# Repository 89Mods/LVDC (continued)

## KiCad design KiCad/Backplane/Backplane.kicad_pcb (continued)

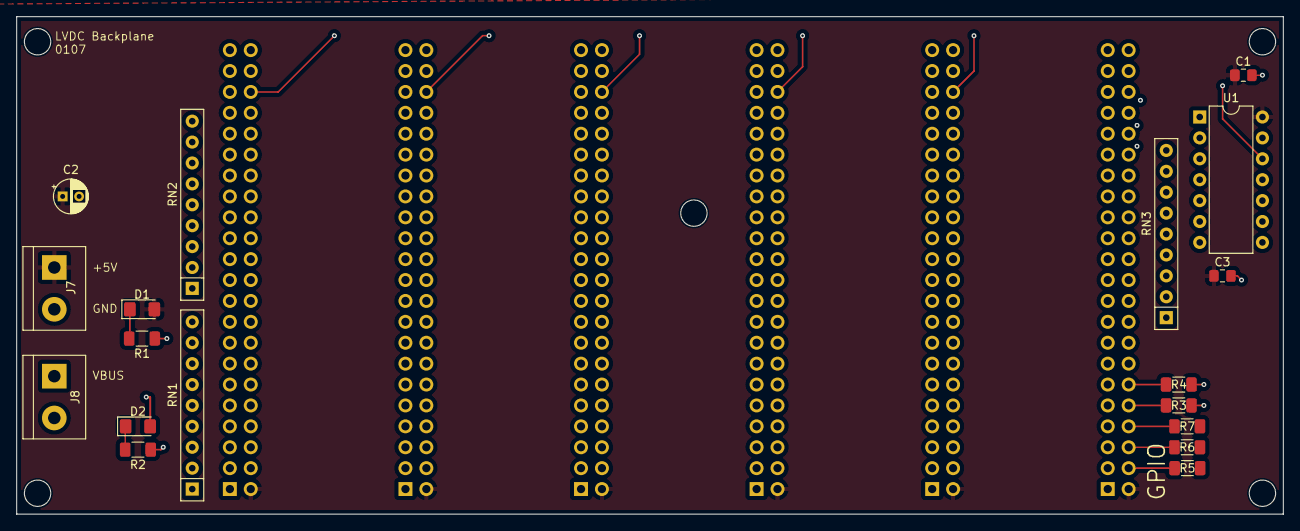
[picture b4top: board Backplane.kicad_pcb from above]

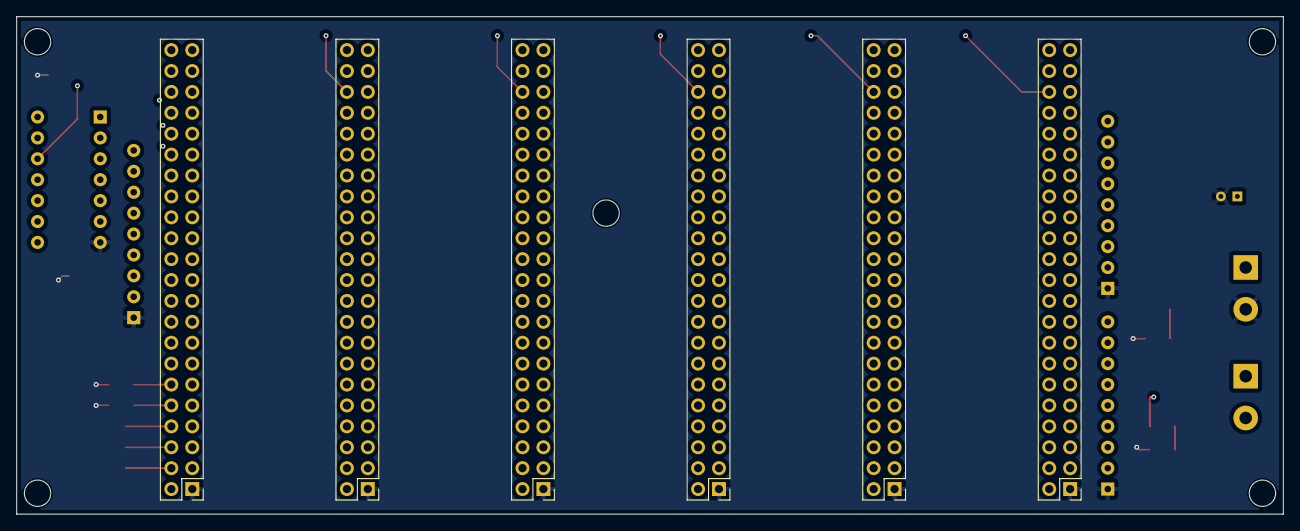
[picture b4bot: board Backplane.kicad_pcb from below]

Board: 4 copper layers, 153.9 x 60.5 mm, 24 parts (6 on the bottom side), 52 nets.

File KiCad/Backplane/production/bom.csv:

Designator,Footprint,Quantity,Value,LCSC Part #
"_5, _4, _3, _2, ",,5,,
C1,0805,1,100nF,
C2,CP_Radial_D4.0mm_P2.00mm,1,10µF,
C3,0805,1,1µF,
"D1, D2",1206,2,LED,
J1,PinHeader_2x22_P2.54mm_Vertical,1,SLOT1,
J2,PinHeader_2x22_P2.54mm_Vertical,1,SLOT2,
J3,PinHeader_2x22_P2.54mm_Vertical,1,SLOT3,
J4,PinHeader_2x22_P2.54mm_Vertical,1,SLOT4,
J5,PinHeader_2x22_P2.54mm_Vertical,1,SLOT5,
J6,PinHeader_2x22_P2.54mm_Vertical,1,GPIO,
"J7, J8",TerminalBlock_bornier-2_P5.08mm,2,Screw_Terminal_01x02,
"R1, R2, R3, R4, R5, R6, R7",1206,7,2K,
"RN1, RN2, RN3",R_Array_SIP9,3,R_Network08,
U1,DIP-14_W7.62mm,1,74HCT04,

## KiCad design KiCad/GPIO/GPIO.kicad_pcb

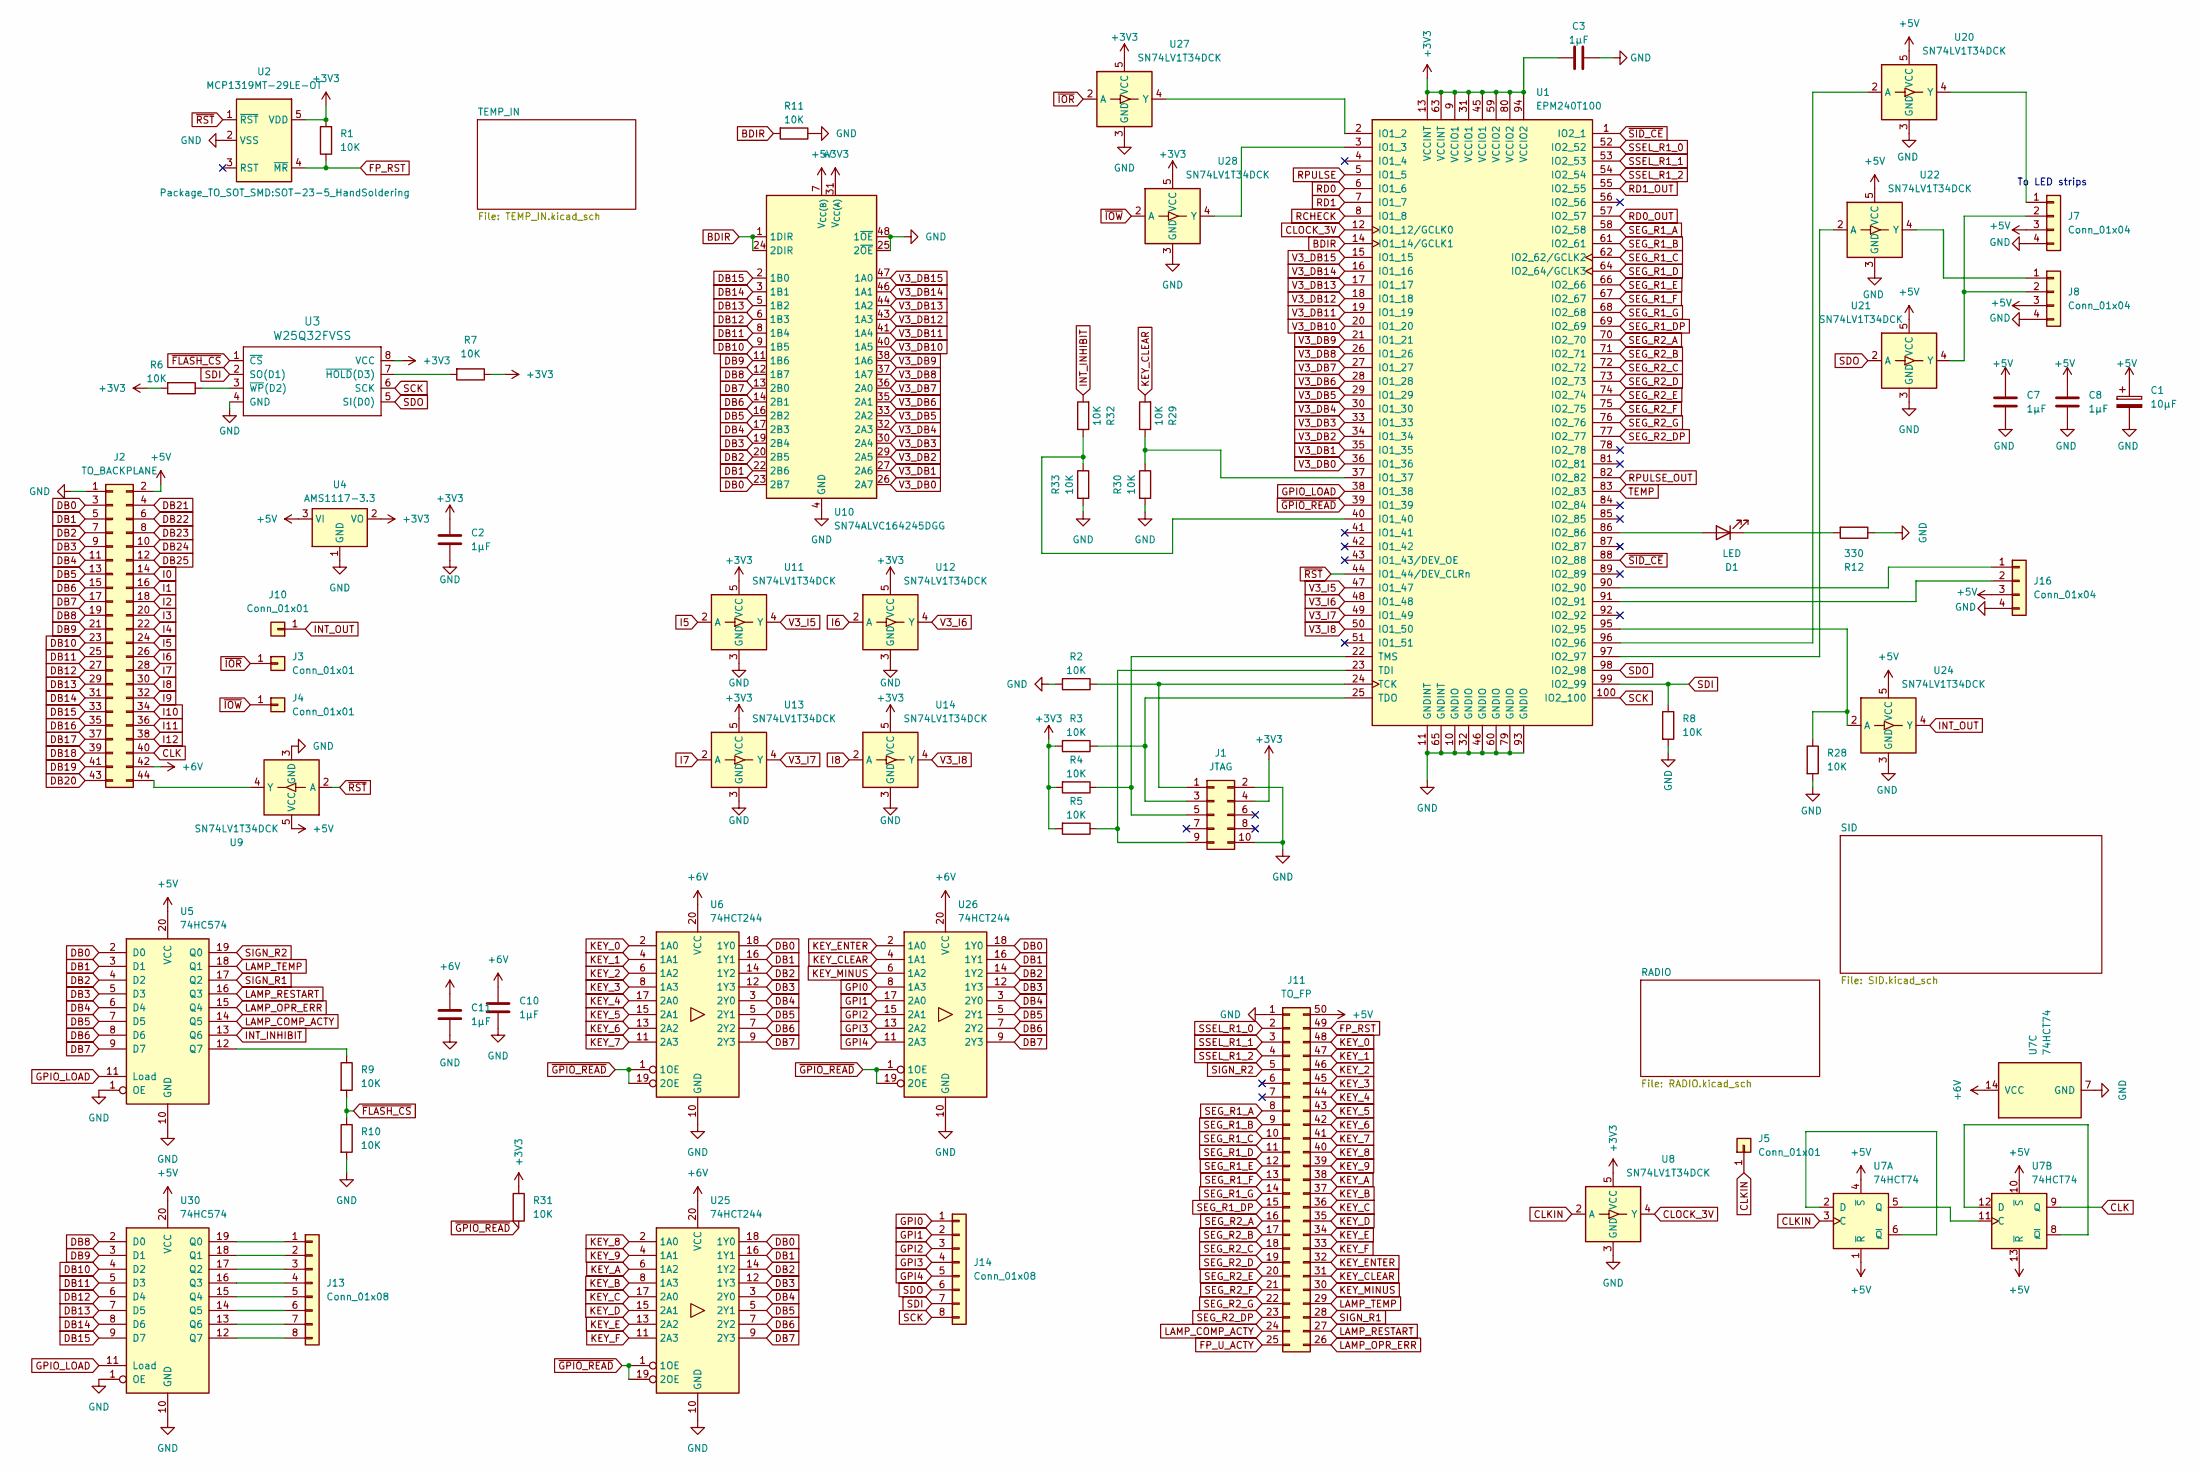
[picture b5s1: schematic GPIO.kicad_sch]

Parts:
C1: 10µF; CP_Radial_D4.0mm_P2.00mm
C2, C3, C7, C8, C10, C11: 1µF; C_0805_2012Metric_Pad1.18x1.45mm_HandSolder
D1: LED; LED_1206_3216Metric_Pad1.42x1.75mm_HandSolder
J1: JTAG; PinHeader_2x05_P2.54mm_Vertical
J2: TO_BACKPLANE; PinHeader_2x22_P2.54mm_Vertical
J3, J4, J5, J10: Conn_01x01; PinHeader_1x01_P2.54mm_Vertical
J7, J8, J16: Conn_01x04; PinHeader_1x04_P2.54mm_Vertical
J11: TO_FP; PinHeader_2x25_P2.54mm_Vertical
J13, J14: Conn_01x08; PinHeader_1x08_P2.54mm_Vertical
R1, R2, R3, R4, R5, R6, R7, R8, R9, R10, R11, R28, R29, R30, R31, R32, R33: 10K; R_1206_3216Metric_Pad1.30x1.75mm_HandSolder
R12: 330; R_1206_3216Metric_Pad1.30x1.75mm_HandSolder
U1: EPM240T100; LQFP-100_14x14mm_P0.5mm
U2: MCP1319MT-29LE-OT; SOT-23-5_HandSoldering
U3: W25Q32FVSS; DIP-8_W7.62mm_Socket; Part # W25Q32JVSSIQ
U4: AMS1117-3.3; SOT-223-3_TabPin2
U5, U30: 74HC574; SO-20_12.8x7.5mm_P1.27mm
U6, U25, U26: 74HCT244; SO-20_12.8x7.5mm_P1.27mm
U7: 74HCT74; SO-14_3.9x8.65mm_P1.27mm
U8, U9, U11, U12, U13, U14, U20, U21, U22, U24, U27, U28: SN74LV1T34DCK; SOT-23-5
U10: SN74ALVC164245DGG; TSSOP-48_6.1x12.5mm_P0.5mm

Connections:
+3V3: C2.2, C3.2, J1.4, R1.2, R3.2, R4.2, R5.2, R6.2, R7.1, R31.1, U1.9 (VCCIO1), U1.13 (VCCINT), U1.31 (VCCIO1), U1.45 (VCCIO1), U1.59 (VCCIO2), U1.63 (VCCINT), U1.80 (VCCIO2), U1.94 (VCCIO2), U2.5 (VDD), U3.8 (VCC), U4.2 (VO), U8.5 (VCC), U10.31 (V_{CC(A)}), U10.42 (V_{CC(A)}), U11.5 (VCC), U12.5 (VCC), U13.5 (VCC), U14.5 (VCC), U27.5 (VCC), U28.5 (VCC); also elsewhere on the board
+5V: C1.1, C7.2, C8.2, J2.2, J7.3, J8.3, J11.50, J16.3, U4.3 (VI), U5.20 (VCC), U7.1 (~R), U7.4 (~S), U7.10 (~S), U7.13 (~R), U9.5 (VCC), U10.7 (V_{CC(B)}), U10.18 (V_{CC(B)}), U20.5 (VCC), U21.5 (VCC), U22.5 (VCC), U24.5 (VCC), U30.20 (VCC); also elsewhere on the board
+6V: C10.2, C11.2, J2.42, U6.20 (VCC), U7.14 (VCC), U25.20 (VCC), U26.20 (VCC)
BDIR: R11.2, U1.14 (IO1_14/GCLK1), U10.1 (1DIR), U10.24 (2DIR)
CLK: J2.40, U7.9 (Q)
CLKIN: J5.1, U7.3 (C), U8.2 (A)
CLOCK_3V: U1.12 (IO1_12/GCLK0), U8.4 (Y)
DB0: J2.3, U5.2 (D0), U6.18 (1Y0), U10.23 (2B7), U25.18 (1Y0), U26.18 (1Y0); also elsewhere on the board
DB1: J2.5, U5.3 (D1), U6.16 (1Y1), U10.22 (2B6), U25.16 (1Y1), U26.16 (1Y1); also elsewhere on the board
DB2: J2.7, U5.4 (D2), U6.14 (1Y2), U10.20 (2B5), U25.14 (1Y2), U26.14 (1Y2); also elsewhere on the board
DB3: J2.9, U5.5 (D3), U6.12 (1Y3), U10.19 (2B4), U25.12 (1Y3), U26.12 (1Y3); also elsewhere on the board
DB4: J2.11, U5.6 (D4), U6.3 (2Y0), U10.17 (2B3), U25.3 (2Y0), U26.3 (2Y0); also elsewhere on the board
DB5: J2.13, U5.7 (D5), U6.5 (2Y1), U10.16 (2B2), U25.5 (2Y1), U26.5 (2Y1); also elsewhere on the board
DB6: J2.15, U5.8 (D6), U6.7 (2Y2), U10.14 (2B1), U25.7 (2Y2), U26.7 (2Y2); also elsewhere on the board
DB7: J2.17, U5.9 (D7), U6.9 (2Y3), U10.13 (2B0), U25.9 (2Y3), U26.9 (2Y3); also elsewhere on the board
DB8: J2.19, U10.12 (1B7), U30.2 (D0); also elsewhere on the board
DB9: J2.21, U10.11 (1B6), U30.3 (D1); also elsewhere on the board
DB10: J2.23, U10.9 (1B5), U30.4 (D2); also elsewhere on the board
DB11: J2.25, U10.8 (1B4), U30.5 (D3); also elsewhere on the board
DB12: J2.27, U10.6 (1B3), U30.6 (D4); also elsewhere on the board
DB13: J2.29, U10.5 (1B2), U30.7 (D5); also elsewhere on the board
DB14: J2.31, U10.3 (1B1), U30.8 (D6)
DB15: J2.33, U10.2 (1B0), U30.9 (D7)
DB16: J2.35
DB17: J2.37
DB18: J2.39
DB19: J2.41
DB20: J2.43
DB21: J2.4
DB22: J2.6
DB23: J2.8
DB24: J2.10
DB25: J2.12
FP_RST: J11.49, R1.1, U2.4 (~MR)
FP_U_ACTY: J11.25; also elsewhere on the board
GND: C1.2, C2.1, C3.1, C7.1, C8.1, C10.1, C11.1, J1.2, J1.10, J2.1, J7.4, J8.4, J11.1, J16.4, R2.2, R8.2, R10.2, R11.1, R12.1, R28.2, R30.2, R33.2, U1.10 (GNDIO), U1.11 (GNDINT), U1.32 (GNDIO), U1.46 (GNDIO), U1.60 (GNDIO), U1.65 (GNDINT), U1.79 (GNDIO), U1.93 (GNDIO), U2.2 (VSS), U3.4 (GND), U4.1 (GND), U5.1 (OE), U5.10 (GND), U6.10 (GND), U7.7 (GND), U8.3 (GND), U9.3 (GND), U10.4 (GND), U10.10 (GND), U10.15 (GND), U10.21 (GND), U10.25 (2~OE), U10.28 (GND), U10.34 (GND), U10.39 (GND), U10.45 (GND), U10.48 (1~OE), U11.3 (GND), U12.3 (GND), U13.3 (GND), U14.3 (GND), U20.3 (GND), U21.3 (GND), U22.3 (GND), U24.3 (GND), U25.10 (GND), U26.10 (GND), U27.3 (GND), U28.3 (GND), U30.1 (OE), U30.10 (GND); also elsewhere on the board
GPI0: J14.1, U26.8 (1A3)
GPI1: J14.2, U26.17 (2A0)
GPI2: J14.3, U26.15 (2A1)
GPI3: J14.4, U26.13 (2A2)
GPI4: J14.5, U26.11 (2A3)
GPIO_LOAD: U1.38 (IO1_38), U5.11 (Load), U30.11 (Load)
I0: J2.14
I1: J2.16
I2: J2.18
I3: J2.20
I4: J2.22
I5: J2.24, U11.2 (A)
I6: J2.26, U12.2 (A)
I7: J2.28, U13.2 (A)
I8: J2.30, U14.2 (A)
I9: J2.32
I10: J2.34
I11: J2.36
I12: J2.38
INT_INHIBIT: R32.2, U5.13 (Q6)
INT_OUT: J10.1, U24.4 (Y)
KEY_0: J11.48, U6.2 (1A0)
KEY_1: J11.47, U6.4 (1A1)
KEY_2: J11.46, U6.6 (1A2)
KEY_3: J11.45, U6.8 (1A3)
KEY_4: J11.44, U6.17 (2A0)
KEY_5: J11.43, U6.15 (2A1)
KEY_6: J11.42, U6.13 (2A2)
KEY_7: J11.41, U6.11 (2A3)
KEY_8: J11.40, U25.2 (1A0)
KEY_9: J11.39, U25.4 (1A1)
KEY_A: J11.38, U25.6 (1A2)
KEY_B: J11.37, U25.8 (1A3)
KEY_C: J11.36, U25.17 (2A0)
KEY_CLEAR: J11.31, R29.2, U26.4 (1A1)
KEY_D: J11.35, U25.15 (2A1)
KEY_E: J11.34, U25.13 (2A2)
KEY_ENTER: J11.32, U26.2 (1A0)
KEY_F: J11.33, U25.11 (2A3)
KEY_MINUS: J11.30, U26.6 (1A2)
LAMP_COMP_ACTY: J11.24, U5.14 (Q5)
LAMP_OPR_ERR: J11.26, U5.15 (Q4)
LAMP_RESTART: J11.27, U5.16 (Q3)
LAMP_TEMP: J11.29, U5.18 (Q1)
unnamed: D1.2 (A), U1.86 (IO2_86)
unnamed: D1.1 (K), R12.2
unnamed: J1.1, R2.1, U1.24 (TCK)
unnamed: J1.3, R3.1, U1.25 (TDO)
unnamed: J1.5, R4.1, U1.22 (TMS)
unnamed: J1.9, R5.1, U1.23 (TDI)
unnamed: J2.44, U9.4 (Y)
unnamed: J7.1, U20.4 (Y)
unnamed: J7.2, J8.2, U21.4 (Y)
unnamed: J8.1, U22.4 (Y)
unnamed: J13.1, U30.19 (Q0)
unnamed: J13.2, U30.18 (Q1)
unnamed: J13.3, U30.17 (Q2)
unnamed: J13.4, U30.16 (Q3)
unnamed: J13.5, U30.15 (Q4)
unnamed: J13.6, U30.14 (Q5)
unnamed: J13.7, U30.13 (Q6)
unnamed: J13.8, U30.12 (Q7)
unnamed: J16.1, U1.90 (IO2_90)
unnamed: J16.2, U1.91 (IO2_91)
unnamed: U1.2 (IO1_2), U27.4 (Y)
unnamed: U1.3 (IO1_3), U28.4 (Y)
unnamed: R29.1, R30.1, U1.37 (IO1_37)
unnamed: R32.1, R33.1, U1.40 (IO1_40)
unnamed: R28.1, U1.95 (IO2_95), U24.2 (A)
unnamed: U1.96 (IO2_96), U20.2 (A)
unnamed: U1.97 (IO2_97), U22.2 (A)
unnamed: R7.2, U3.7 (~HOLD(D3))
unnamed: R6.1, U3.3 (~WP(D2))
unnamed: R9.1, U5.12 (Q7)
unnamed: U7.2 (D), U7.6 (~Q)
unnamed: U7.5 (Q), U7.11 (C)
unnamed: U7.8 (~Q), U7.12 (D)
RCHECK: U1.8 (IO1_8); also elsewhere on the board
RD0: U1.6 (IO1_6); also elsewhere on the board
RD0_OUT: U1.57 (IO2_57); also elsewhere on the board
RD1: U1.7 (IO1_7); also elsewhere on the board
RD1_OUT: U1.55 (IO2_55); also elsewhere on the board
RPULSE: U1.5 (IO1_5); also elsewhere on the board
RPULSE_OUT: U1.82 (IO2_82); also elsewhere on the board
SCK: J14.8, U1.100 (IO2_100), U3.6 (SCK)
SDI: J14.7, R8.1, U1.99 (IO2_99), U3.2 (SO(D1))
SDO: J14.6, U1.98 (IO2_98), U3.5 (SI(D0)), U21.2 (A)
SEG_R1_A: J11.8, U1.58 (IO2_58)
SEG_R1_B: J11.9, U1.61 (IO2_61)
SEG_R1_C: J11.10, U1.62 (IO2_62/GCLK2)
SEG_R1_D: J11.11, U1.64 (IO2_64/GCLK3)
SEG_R1_DP: J11.15, U1.69 (IO2_69)
SEG_R1_E: J11.12, U1.66 (IO2_66)
SEG_R1_F: J11.13, U1.67 (IO2_67)
SEG_R1_G: J11.14, U1.68 (IO2_68)
SEG_R2_A: J11.16, U1.70 (IO2_70)
SEG_R2_B: J11.17, U1.71 (IO2_71)
SEG_R2_C: J11.18, U1.72 (IO2_72)
SEG_R2_D: J11.19, U1.73 (IO2_73)
SEG_R2_DP: J11.23, U1.77 (IO2_77)
SEG_R2_E: J11.20, U1.74 (IO2_74)
SEG_R2_F: J11.21, U1.75 (IO2_75)
SEG_R2_G: J11.22, U1.76 (IO2_76)
SIGN_R1: J11.28, U5.17 (Q2)
SIGN_R2: J11.5, U5.19 (Q0)
SSEL_R1_0: J11.2, U1.52 (IO2_52)
SSEL_R1_1: J11.3, U1.53 (IO2_53)
SSEL_R1_2: J11.4, U1.54 (IO2_54)
TEMP: U1.83 (IO2_83); also elsewhere on the board
V3_DB0: U1.36 (IO1_36), U10.26 (2A7)
V3_DB1: U1.35 (IO1_35), U10.27 (2A6)
V3_DB2: U1.34 (IO1_34), U10.29 (2A5)
V3_DB3: U1.33 (IO1_33), U10.30 (2A4)
V3_DB4: U1.30 (IO1_30), U10.32 (2A3)
V3_DB5: U1.29 (IO1_29), U10.33 (2A2)
V3_DB6: U1.28 (IO1_28), U10.35 (2A1)
V3_DB7: U1.27 (IO1_27), U10.36 (2A0)
V3_DB8: U1.26 (IO1_26), U10.37 (1A7)
V3_DB9: U1.21 (IO1_21), U10.38 (1A6)
V3_DB10: U1.20 (IO1_20), U10.40 (1A5)
V3_DB11: U1.19 (IO1_19), U10.41 (1A4)
V3_DB12: U1.18 (IO1_18), U10.43 (1A3)
V3_DB13: U1.17 (IO1_17), U10.44 (1A2)
V3_DB14: U1.16 (IO1_16), U10.46 (1A1)
V3_DB15: U1.15 (IO1_15), U10.47 (1A0)
V3_I5: U1.47 (IO1_47), U11.4 (Y)
V3_I6: U1.48 (IO1_48), U12.4 (Y)
V3_I7: U1.49 (IO1_49), U13.4 (Y)
V3_I8: U1.50 (IO1_50), U14.4 (Y)
~FLASH_CS: R9.2, R10.1, U3.1 (~CS)
~GPIO_READ: R31.2, U1.39 (IO1_39), U6.1 (1OE), U6.19 (2OE), U25.1 (1OE), U25.19 (2OE), U26.1 (1OE), U26.19 (2OE)
~IOR: J3.1, U27.2 (A)
~IOW: J4.1, U28.2 (A); also elsewhere on the board
~RST: U1.44 (IO1_44/DEV_CLRn), U2.1 (~RST), U9.2 (A)
~SID_CE: U1.1 (IO2_1), U1.88 (IO2_88); also elsewhere on the board

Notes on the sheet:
To LED strips

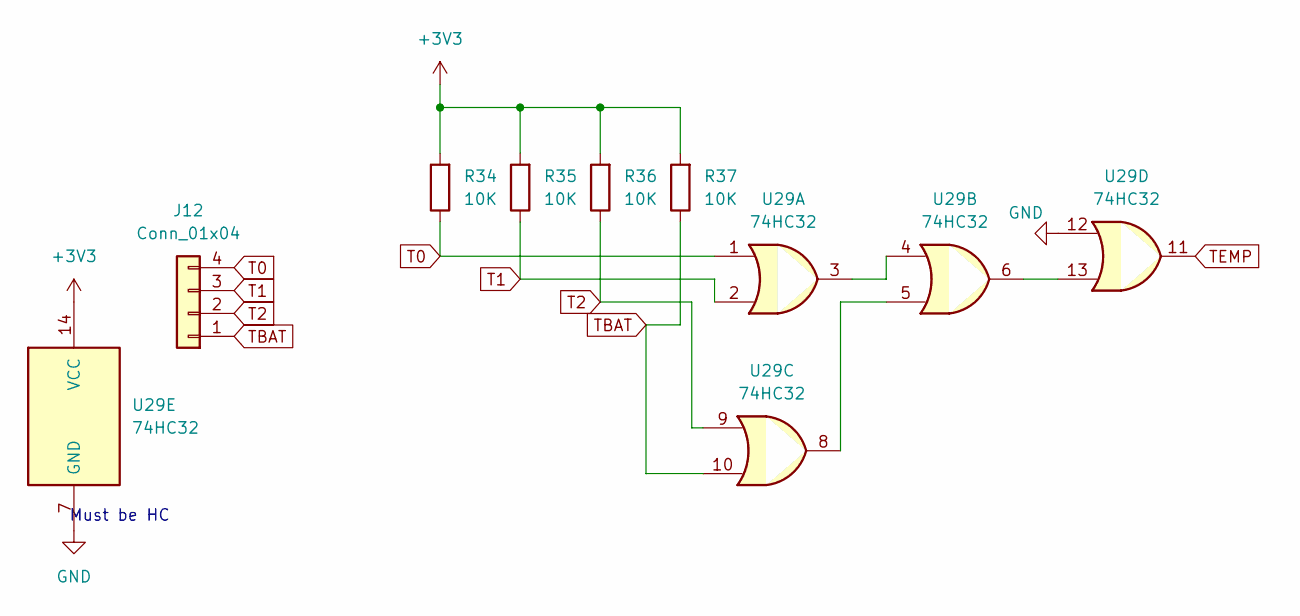
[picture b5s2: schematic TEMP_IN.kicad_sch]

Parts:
J12: Conn_01x04; PinHeader_1x04_P2.54mm_Vertical
R34, R35, R36, R37: 10K; R_1206_3216Metric_Pad1.30x1.75mm_HandSolder
U29: 74HC32; SO-14_3.9x8.65mm_P1.27mm

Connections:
+3V3: R34.2, R35.2, R36.2, R37.2, U29.14 (VCC); also elsewhere on the board
GND: U29.7 (GND), U29.12; also elsewhere on the board
unnamed: U29.3, U29.4
unnamed: U29.5, U29.8
unnamed: U29.6, U29.13
T0: J12.4, R34.1, U29.1
T1: J12.3, R35.1, U29.2
T2: J12.2, R36.1, U29.9
TBAT: J12.1, R37.1, U29.10
TEMP: U29.11; also elsewhere on the board

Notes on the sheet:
Must be HC

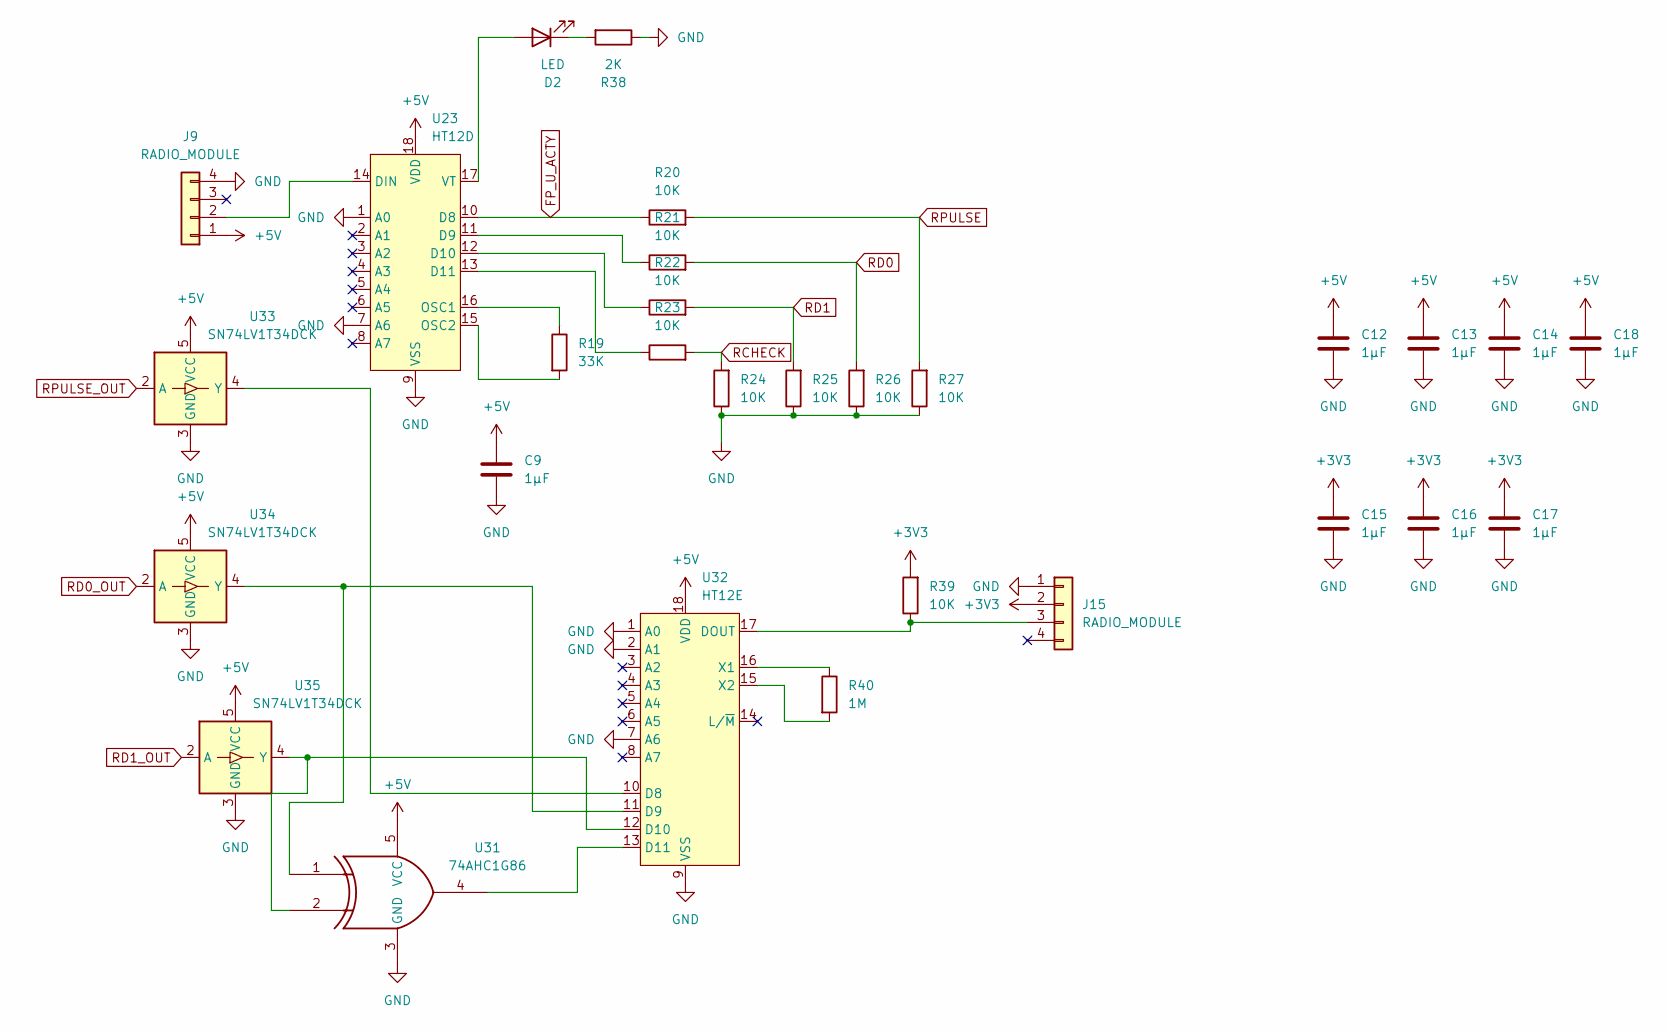
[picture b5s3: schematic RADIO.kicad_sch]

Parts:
C9, C12, C13, C14, C15, C16, C17, C18: 1µF; C_0805_2012Metric_Pad1.18x1.45mm_HandSolder
D2: LED; LED_1206_3216Metric_Pad1.42x1.75mm_HandSolder
J9, J15: RADIO_MODULE; PinSocket_1x04_P2.54mm_Vertical
R19: 33K; R_1206_3216Metric_Pad1.30x1.75mm_HandSolder
R20, R21, R22, R23, R24, R25, R26, R27, R39: 10K; R_1206_3216Metric_Pad1.30x1.75mm_HandSolder
R38: 2K; R_1206_3216Metric_Pad1.30x1.75mm_HandSolder
R40: 1M; R_1206_3216Metric_Pad1.30x1.75mm_HandSolder
U23: HT12D; DIP-18_W7.62mm
U31: 74AHC1G86; SOT-23-5_HandSoldering
U32: HT12E; DIP-18_W7.62mm
U33, U34, U35: SN74LV1T34DCK; SOT-23-5

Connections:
+3V3: C15.2, C16.2, C17.2, J15.2, R39.2; also elsewhere on the board
+5V: C9.2, C12.2, C13.2, C14.2, C18.2, J9.1, U23.18 (VDD), U31.5 (VCC), U32.18 (VDD), U33.5 (VCC), U34.5 (VCC), U35.5 (VCC); also elsewhere on the board
FP_U_ACTY: R20.1, U23.10 (D8); also elsewhere on the board
GND: C9.1, C12.1, C13.1, C14.1, C15.1, C16.1, C17.1, C18.1, J9.4, J15.1, R24.1, R25.1, R26.1, R27.1, R38.1, U23.1 (A0), U23.7 (A6), U23.9 (VSS), U31.3 (GND), U32.1 (A0), U32.2 (A1), U32.7 (A6), U32.9 (VSS), U33.3 (GND), U34.3 (GND), U35.3 (GND); also elsewhere on the board
unnamed: D2.2 (A), U23.17 (VT)
unnamed: D2.1 (K), R38.2
unnamed: J9.2, U23.14 (DIN)
unnamed: J15.3, R39.1, U32.17 (DOUT)
unnamed: R21.1, U23.11 (D9)
unnamed: R22.1, U23.12 (D10)
unnamed: R23.1, U23.13 (D11)
unnamed: R19.1, U23.16 (OSC1)
unnamed: R19.2, U23.15 (OSC2)
unnamed: U32.10 (D8), U33.4 (Y)
unnamed: U31.1, U32.11 (D9), U34.4 (Y)
unnamed: U31.2, U32.12 (D10), U35.4 (Y)
unnamed: U31.4, U32.13 (D11)
unnamed: R40.1, U32.16 (X1)
unnamed: R40.2, U32.15 (X2)
RCHECK: R23.2, R24.2; also elsewhere on the board
RD0: R21.2, R26.2; also elsewhere on the board
RD0_OUT: U34.2 (A); also elsewhere on the board
RD1: R22.2, R25.2; also elsewhere on the board
RD1_OUT: U35.2 (A); also elsewhere on the board
RPULSE: R20.2, R27.2; also elsewhere on the board
RPULSE_OUT: U33.2 (A); also elsewhere on the board

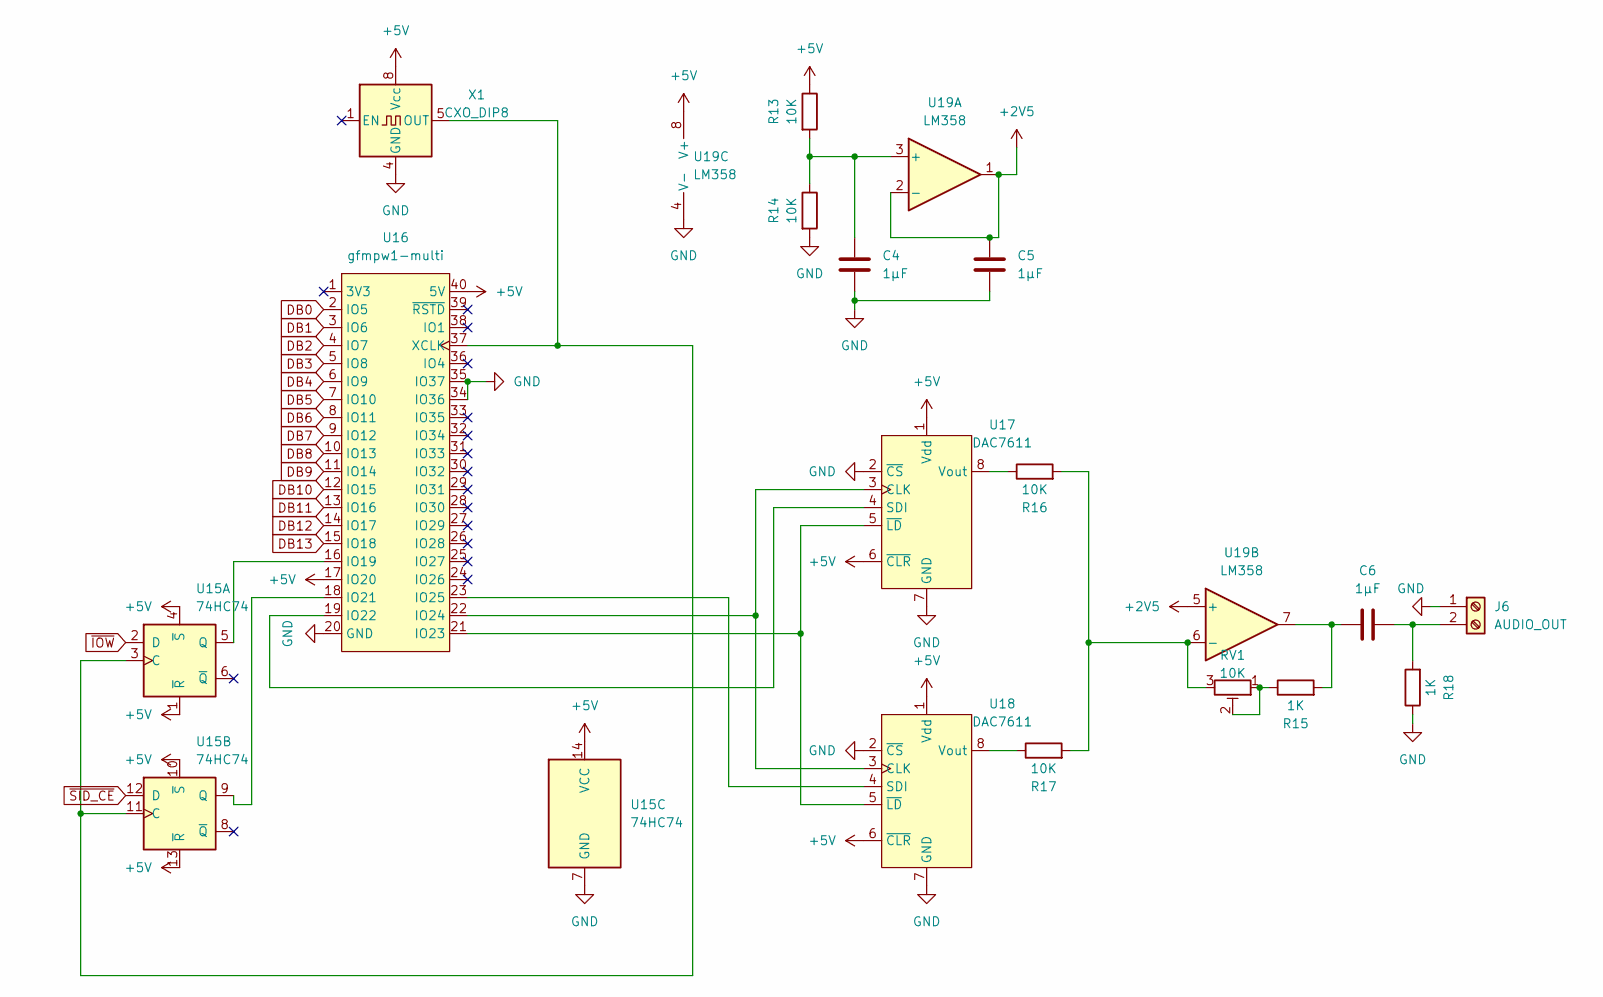
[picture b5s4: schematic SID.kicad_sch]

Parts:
C4, C5, C6: 1µF; C_0805_2012Metric_Pad1.18x1.45mm_HandSolder
J6: AUDIO_OUT; TerminalBlock_bornier-2_P5.08mm
R13, R14, R16, R17: 10K; R_1206_3216Metric_Pad1.30x1.75mm_HandSolder
R15, R18: 1K; R_1206_3216Metric_Pad1.30x1.75mm_HandSolder
RV1: 10K; Potentiometer_ACP_CA9-V10_Vertical
U15: 74HC74; SO-14_3.9x8.65mm_P1.27mm
U16: gfmpw1-multi; DIP-40_W15.24mm_Socket
U17, U18: DAC7611; DIP-8_W7.62mm
U19: LM358; DIP-8_W7.62mm
X1: CXO_DIP8; Oscillator_DIP-8

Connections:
+2V5: C5.2, U19.1, U19.2 (-), U19.5 (+)
+5V: R13.1, U15.1 (~R), U15.4 (~S), U15.10 (~S), U15.13 (~R), U15.14 (VCC), U16.17 (IO20), U16.40 (5V), U17.1 (Vdd), U17.6 (~CLR), U18.1 (Vdd), U18.6 (~CLR), U19.8 (V+), X1.8 (Vcc); also elsewhere on the board
DB0: U16.2 (IO5); also elsewhere on the board
DB1: U16.3 (IO6); also elsewhere on the board
DB2: U16.4 (IO7); also elsewhere on the board
DB3: U16.5 (IO8); also elsewhere on the board
DB4: U16.6 (IO9); also elsewhere on the board
DB5: U16.7 (IO10); also elsewhere on the board
DB6: U16.8 (IO11); also elsewhere on the board
DB7: U16.9 (IO12); also elsewhere on the board
DB8: U16.10 (IO13); also elsewhere on the board
DB9: U16.11 (IO14); also elsewhere on the board
DB10: U16.12 (IO15); also elsewhere on the board
DB11: U16.13 (IO16); also elsewhere on the board
DB12: U16.14 (IO17); also elsewhere on the board
DB13: U16.15 (IO18); also elsewhere on the board
GND: C4.1, C5.1, J6.1, R14.2, R18.1, U15.7 (GND), U16.20 (GND), U16.34 (IO36), U16.35 (IO37), U17.2 (~CS), U17.7 (GND), U18.2 (~CS), U18.7 (GND), U19.4 (V-), X1.4 (GND); also elsewhere on the board
unnamed: C6.2, R15.2, U19.7
unnamed: C6.1, J6.2, R18.2
unnamed: R15.1, RV1.1, RV1.2
unnamed: U15.3 (C), U15.11 (C), U16.37 (XCLK), X1.5 (OUT)
unnamed: U15.5 (Q), U16.16 (IO19)
unnamed: U15.9 (Q), U16.18 (IO21)
unnamed: U16.19 (IO22), U17.4 (SDI)
unnamed: U16.21 (IO23), U17.5 (~LD), U18.5 (~LD)
unnamed: U16.22 (IO24), U17.3 (CLK), U18.3 (CLK)
unnamed: U16.23 (IO25), U18.4 (SDI)
unnamed: R16.1, U17.8 (Vout)
unnamed: R17.1, U18.8 (Vout)
unnamed: C4.2, R13.2, R14.1, U19.3 (+)
unnamed: R16.2, R17.2, RV1.3, U19.6 (-)
~IOW: U15.2 (D); also elsewhere on the board
~SID_CE: U15.12 (D); also elsewhere on the board

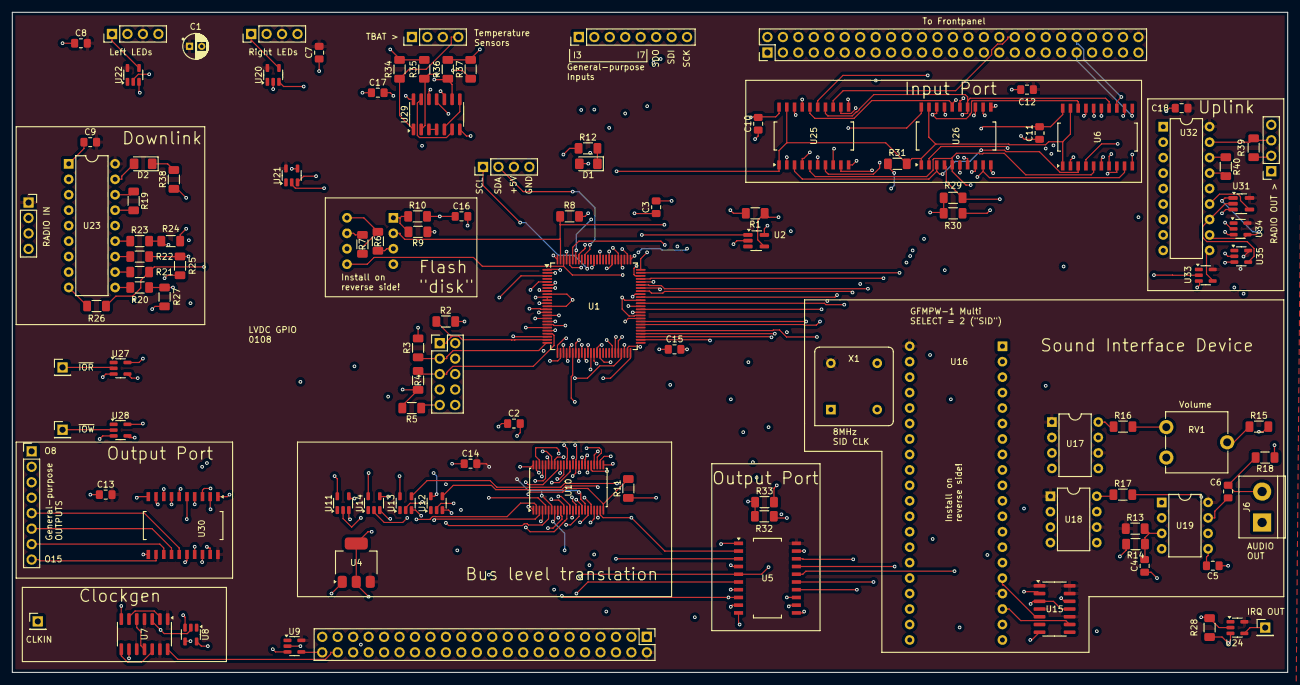
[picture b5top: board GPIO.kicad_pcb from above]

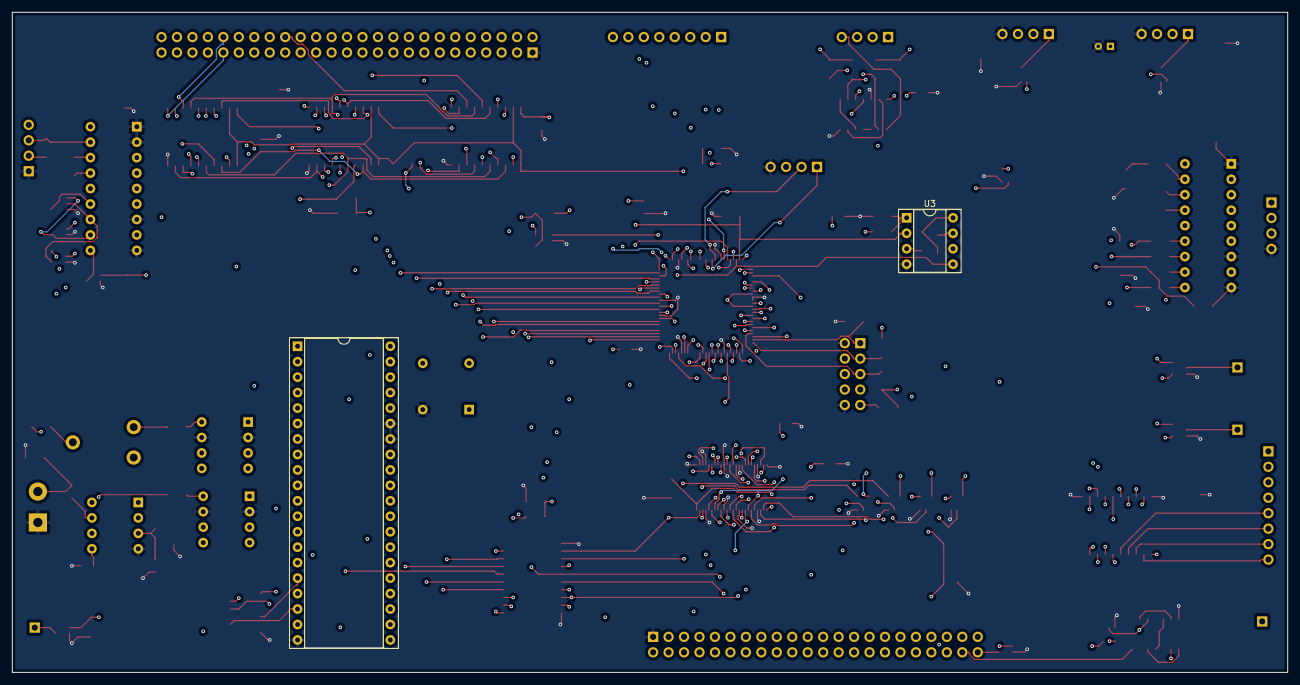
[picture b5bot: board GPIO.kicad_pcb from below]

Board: 4 copper layers, 209.6 x 108.5 mm, 113 parts (2 on the bottom side), 189 nets.

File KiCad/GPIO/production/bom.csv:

Designator,Footprint,Quantity,Value,LCSC Part #
C1,CP_Radial_D4.0mm_P2.00mm,1,10µF,
"C10, C11, C12, C13, C14, C15, C16, C17, C18, C2, C3, C4, C5, C6, C7, C8, C9",0805,17,1µF,
"D1, D2",1206,2,LED,
J1,PinHeader_2x05_P2.54mm_Vertical,1,JTAG,
"J10, J3, J4, J5",PinHeader_1x01_P2.54mm_Vertical,4,Conn_01x01,
J11,PinHeader_2x25_P2.54mm_Vertical,1,TO_FP,
"J12, J16, J7, J8",PinHeader_1x04_P2.54mm_Vertical,4,Conn_01x04,
"J13, J14",PinHeader_1x08_P2.54mm_Vertical,2,Conn_01x08,
"J15, J9",PinSocket_1x04_P2.54mm_Vertical,2,RADIO_MODULE,
J2,PinHeader_2x22_P2.54mm_Vertical,1,TO_BACKPLANE,
J6,TerminalBlock_bornier-2_P5.08mm,1,AUDIO_OUT,
"R1, R10, R11, R13, R14, R16, R17, R2, R20, R21, R22, R23, R24, R25, R26, R27, R28, R29, R3, R30, R31, R32, R33, R34, R35, R36, R37, R39, R4, R5, R6, R7, R8, R9",1206,34,10K,
R12,1206,1,330,
"R15, R18",1206,2,1K,
R19,1206,1,33K,
R38,1206,1,2K,
R40,1206,1,1M,
RV1,Potentiometer_ACP_CA9-V10_Vertical,1,10K,
U1,LQFP-100_14x14mm_P0.5mm,1,EPM240T100,
U10,TSSOP-48_6.1x12.5mm_P0.5mm,1,SN74ALVC164245DGG,
"U11, U12, U13, U14, U20, U21, U22, U24, U27, U28, U33, U34, U35, U8, U9",SOT-23-5,15,SN74LV1T34DCK,
U15,SO-14_3.9x8.65mm_P1.27mm,1,74HC74,
U16,DIP-40_W15.24mm_Socket,1,gfmpw1-multi,
"U17, U18",DIP-8_W7.62mm,2,DAC7611,
U19,DIP-8_W7.62mm,1,LM358,
U2,SOT-23-5_HandSoldering,1,MCP1319MT-29LE-OT,
U23,DIP-18_W7.62mm,1,HT12D,
"U25, U26, U6",SO-20_12.8x7.5mm_P1.27mm,3,74HCT244,
U29,SO-14_3.9x8.65mm_P1.27mm,1,74HC32,
U3,DIP-8_W7.62mm_Socket,1,W25Q32FVSS,
"U30, U5",SO-20_12.8x7.5mm_P1.27mm,2,74HC574,
U31,SOT-23-5_HandSoldering,1,74AHC1G86,
U32,DIP-18_W7.62mm,1,HT12E,
U4,SOT-223-3_TabPin2,1,AMS1117-3.3,
U7,SO-14_3.9x8.65mm_P1.27mm,1,74HCT74,
X1,Oscillator_DIP-8,1,CXO_DIP8,
